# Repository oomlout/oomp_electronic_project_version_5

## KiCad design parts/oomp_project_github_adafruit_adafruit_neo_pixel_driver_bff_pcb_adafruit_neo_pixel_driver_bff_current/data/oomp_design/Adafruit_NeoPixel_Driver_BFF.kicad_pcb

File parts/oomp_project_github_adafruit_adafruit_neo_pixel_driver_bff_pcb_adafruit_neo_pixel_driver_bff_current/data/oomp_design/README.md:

# OOMP KiCad design copy

Open `Adafruit_NeoPixel_Driver_BFF.kicad_pro` (or the `.kicad_pcb` / `.kicad_sch`) in KiCad. Local OOMP libraries are under `libraries/`. Original inputs are preserved in [../original/](../original/).

Only verified unchanged installed KiCad defaults were renamed. Modified, custom, unmatched and unavailable items remain unchanged. Soldering variants are never swapped during conversion. Existing pad coordinates, nets and UUIDs are preserved.

See [conversion_report.yaml](conversion_report.yaml) for every conversion and skip. Copy this directory before editing; regeneration refuses to overwrite edited design files.

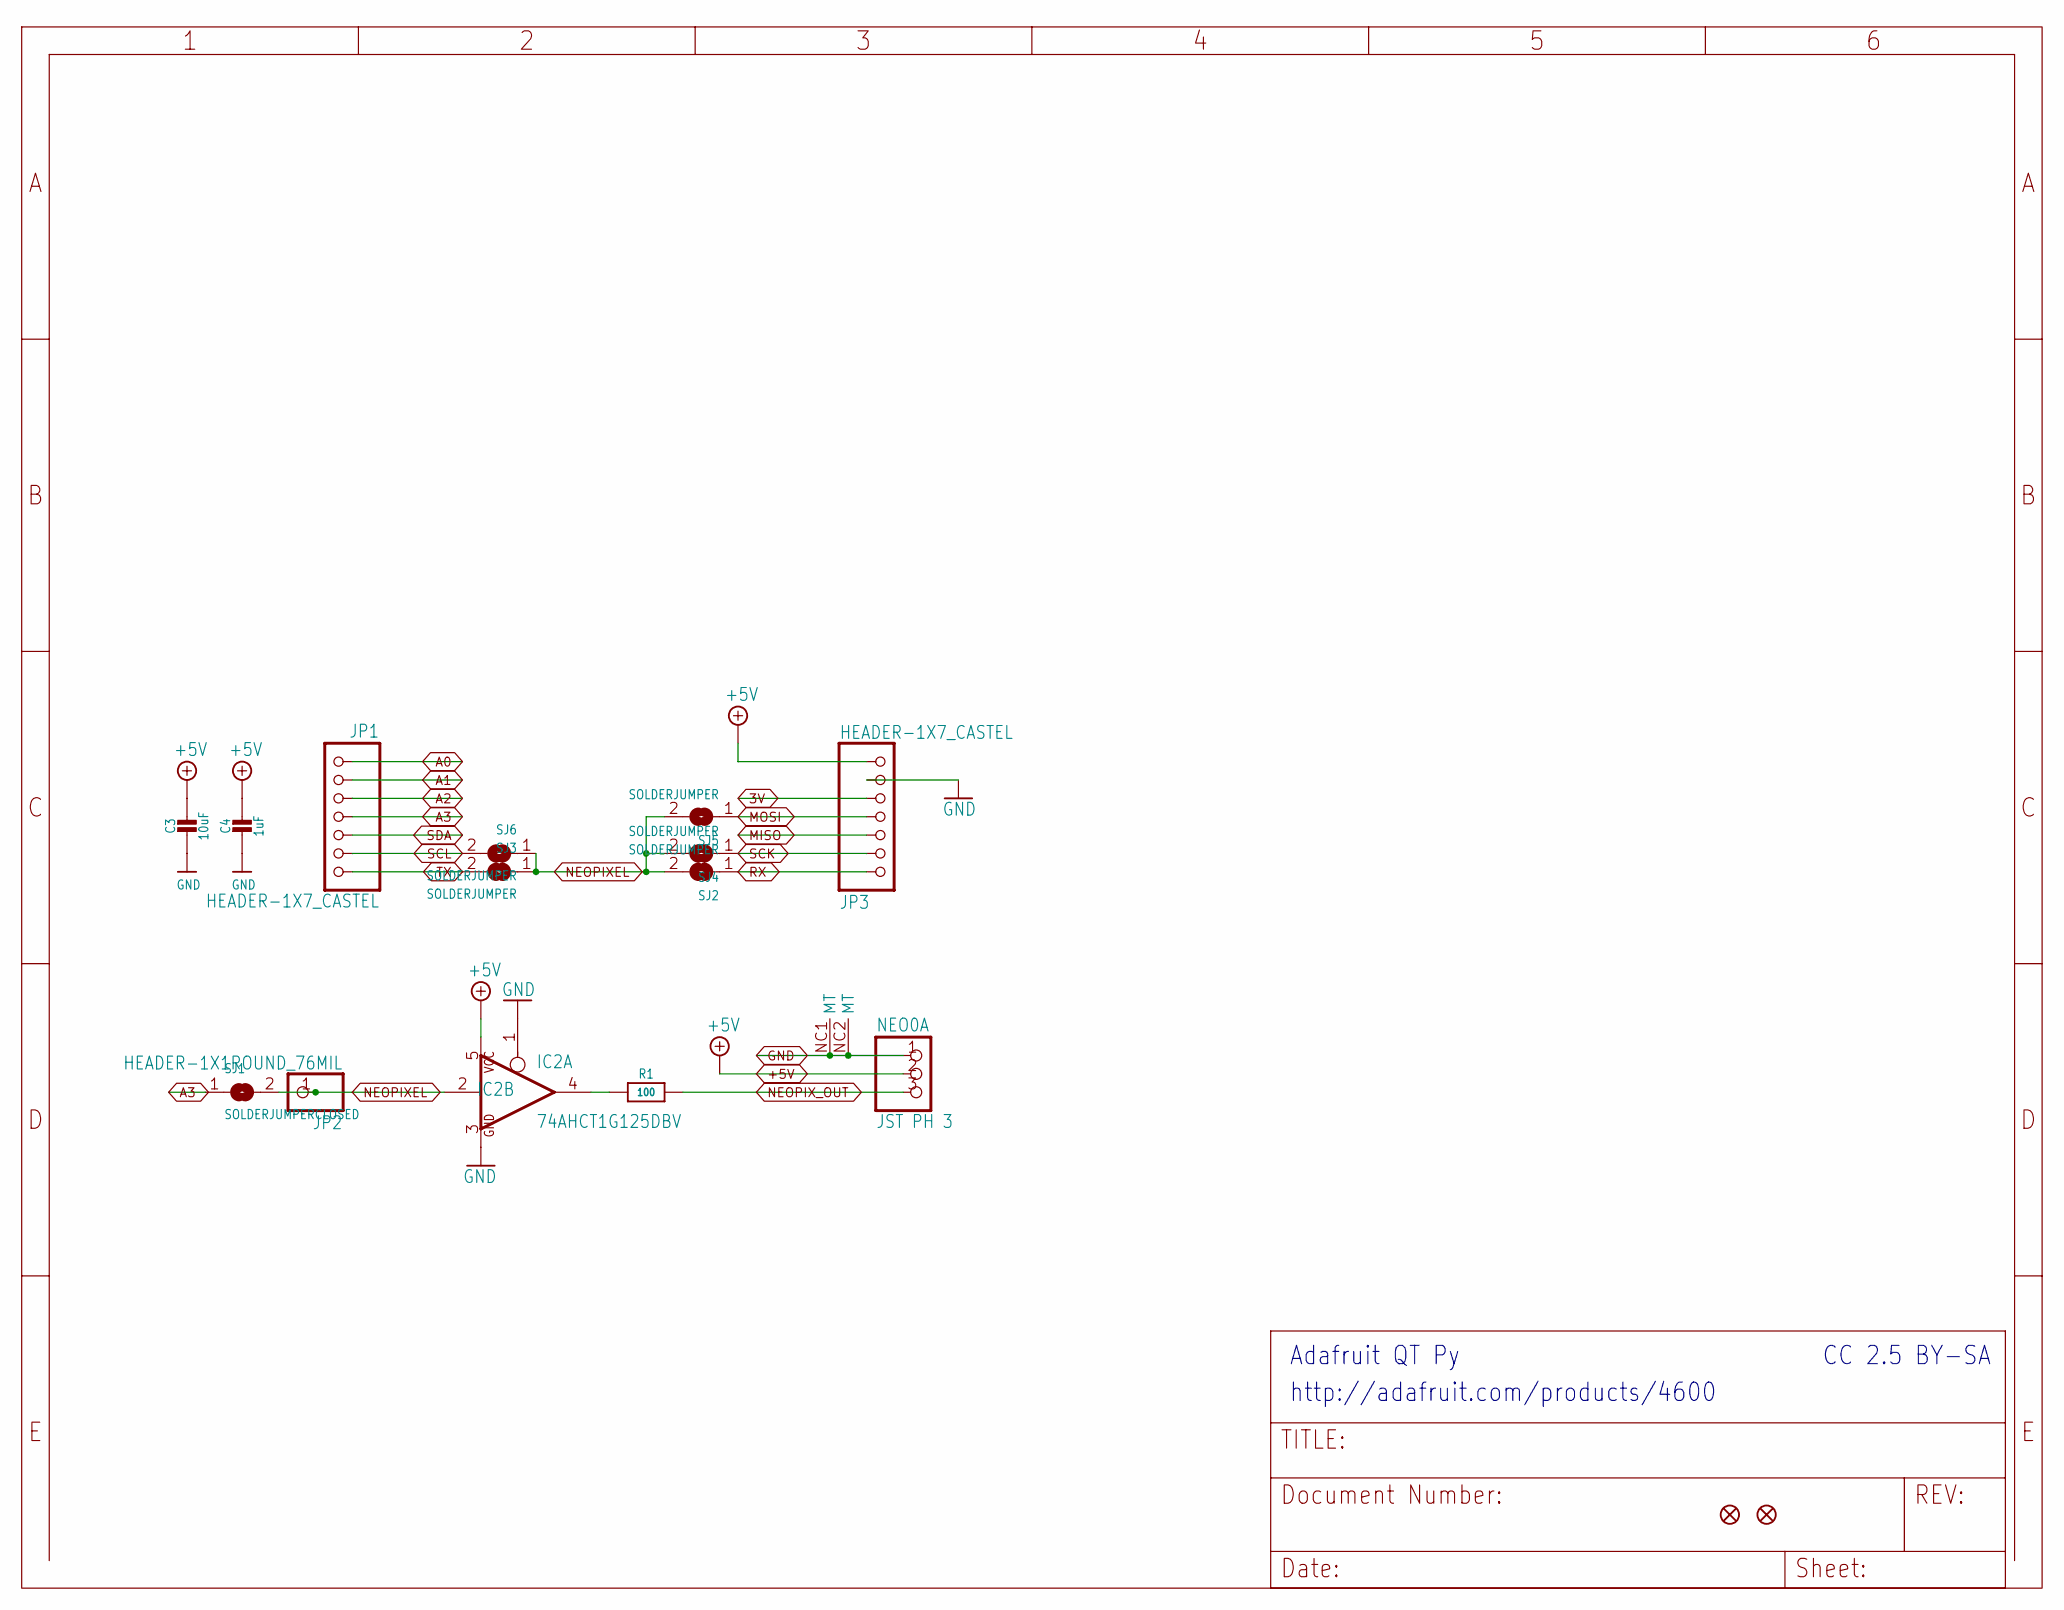
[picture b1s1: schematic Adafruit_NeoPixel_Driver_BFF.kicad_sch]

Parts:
C3: 10uF; 0805-NO
C4: 1uF; 0603-NO
IC2: 74AHCT1G125DBV; SOT23-5
JP1, JP3: HEADER-1X7_CASTEL; 1X07_CASTEL
JP2: HEADER-1X1ROUND_76MIL; 1X01_ROUND_76MIL
NEO0: JST PH 3; JSTPH3
R1: 100; 0603-NO
SJ1: SOLDERJUMPERCLOSED; SOLDERJUMPER_CLOSEDWIRE
SJ2, SJ3, SJ4, SJ5, SJ6: SOLDERJUMPER; SOLDERJUMPER_ARROW_NOPASTE
U$6, U$8: FIDUCIAL_1MM

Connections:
3V: JP3.5, JP3.5C (5)
+5V: C3.1, C4.1, IC2.5 (VCC), JP3.7, JP3.7C (7), NEO0.2
A0: JP1.1, JP1.1C (1)
A1: JP1.2, JP1.2C (2)
A2: JP1.3, JP1.3C (3)
A3: JP1.4, JP1.4C (4), SJ1.1
GND: C3.2, C4.2, IC2.1 (OE), IC2.3 (GND), JP3.6, JP3.6C (6), NEO0.1, NEO0.NC1 (MT), NEO0.NC2 (MT)
MISO: JP3.3, JP3.3C (3)
MOSI: JP3.4, JP3.4C (4), SJ5.1
unnamed: IC2.4 (O), R1.1
NEOPIXEL: IC2.2 (I), JP2.1, SJ1.2, SJ2.2, SJ3.1, SJ4.2, SJ5.2, SJ6.1
NEOPIX_OUT: NEO0.3, R1.2
RX: JP3.1, JP3.1C (1), SJ2.1
SCK: JP3.2, JP3.2C (2), SJ4.1
SCL: JP1.6, JP1.6C (6), SJ6.2
SDA: JP1.5, JP1.5C (5)
TX: JP1.7, JP1.7C (7), SJ3.2

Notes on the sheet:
Adafruit QT Py
http://adafruit.com/products/4600
CC 2.5 BY-SA

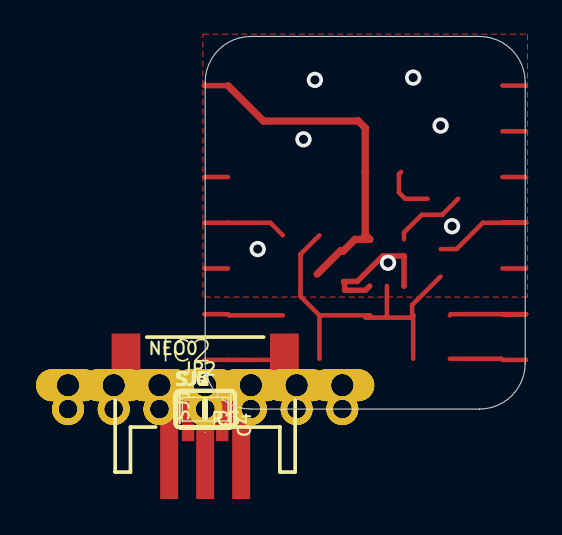
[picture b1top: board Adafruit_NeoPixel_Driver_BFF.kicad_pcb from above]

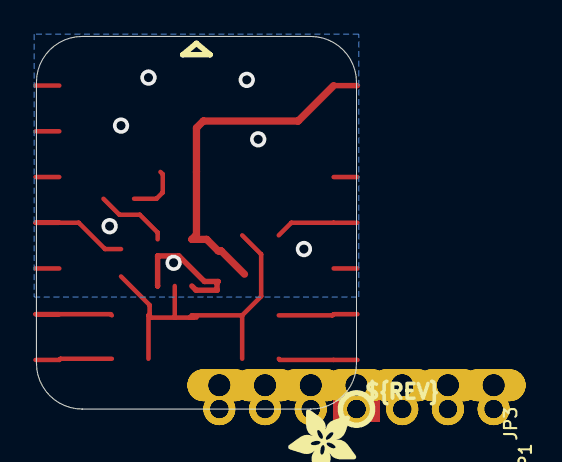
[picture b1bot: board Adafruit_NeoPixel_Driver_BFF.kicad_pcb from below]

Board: 16 copper layers, 17.8 x 20.7 mm, 39 parts (6 on the bottom side), 17 nets.

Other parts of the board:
PLABEL0: PLABEL0
PLABEL1: PLABEL1
PLABEL2: PLABEL2
PLABEL3: PLABEL3
PLABEL4: PLABEL4
PLABEL5: PLABEL5
PLABEL6: PLABEL6
PLABEL7: PLABEL7
PLABEL8: PLABEL8
PLABEL9: PLABEL9
PLABEL10: PLABEL10
PLABEL11: PLABEL11
PLABEL12: PLABEL12
PLABEL13: PLABEL13
PLABEL14: PLABEL14
PLABEL15: PLABEL15
PLABEL16: PLABEL16
PLABEL17: PLABEL17
PLABEL18: PLABEL18
PLABEL19: PLABEL19
PLABEL20: PLABEL20
U$2: ADAFRUIT_3.5MM
U$3: PCBFEAT-REV-040

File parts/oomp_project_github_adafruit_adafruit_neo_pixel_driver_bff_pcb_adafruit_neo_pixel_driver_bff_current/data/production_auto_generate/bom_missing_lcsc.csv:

Designator,Comment,Footprint,OOMP ID,Reason
C3,10uF,Adafruit_NeoPixel_Driver_BFF-import-fps:0805-NO,electronic_capacitor_0805_10_micro_farad,No verified LCSC part number
IC2,74AHCT1G125DBV,Adafruit_NeoPixel_Driver_BFF-import-fps:SOT23-5,,No verified LCSC part number
NEO0,JST PH 3,Adafruit_NeoPixel_Driver_BFF-import-fps:JSTPH3,,No verified LCSC part number
PLABEL0,,Adafruit_NeoPixel_Driver_BFF-import-fps:PLABEL0,,No verified LCSC part number
PLABEL1,,Adafruit_NeoPixel_Driver_BFF-import-fps:PLABEL1,,No verified LCSC part number
PLABEL2,,Adafruit_NeoPixel_Driver_BFF-import-fps:PLABEL2,,No verified LCSC part number
PLABEL3,,Adafruit_NeoPixel_Driver_BFF-import-fps:PLABEL3,,No verified LCSC part number
PLABEL4,,Adafruit_NeoPixel_Driver_BFF-import-fps:PLABEL4,,No verified LCSC part number
PLABEL5,,Adafruit_NeoPixel_Driver_BFF-import-fps:PLABEL5,,No verified LCSC part number
PLABEL6,,Adafruit_NeoPixel_Driver_BFF-import-fps:PLABEL6,,No verified LCSC part number
PLABEL7,,Adafruit_NeoPixel_Driver_BFF-import-fps:PLABEL7,,No verified LCSC part number
PLABEL8,,Adafruit_NeoPixel_Driver_BFF-import-fps:PLABEL8,,No verified LCSC part number
PLABEL9,,Adafruit_NeoPixel_Driver_BFF-import-fps:PLABEL9,,No verified LCSC part number
PLABEL10,,Adafruit_NeoPixel_Driver_BFF-import-fps:PLABEL10,,No verified LCSC part number
PLABEL11,,Adafruit_NeoPixel_Driver_BFF-import-fps:PLABEL11,,No verified LCSC part number
PLABEL12,,Adafruit_NeoPixel_Driver_BFF-import-fps:PLABEL12,,No verified LCSC part number
PLABEL13,,Adafruit_NeoPixel_Driver_BFF-import-fps:PLABEL13,,No verified LCSC part number
PLABEL14,,Adafruit_NeoPixel_Driver_BFF-import-fps:PLABEL14,,No verified LCSC part number
PLABEL15,,Adafruit_NeoPixel_Driver_BFF-import-fps:PLABEL15,,No verified LCSC part number
PLABEL16,,Adafruit_NeoPixel_Driver_BFF-import-fps:PLABEL16,,No verified LCSC part number
PLABEL17,,Adafruit_NeoPixel_Driver_BFF-import-fps:PLABEL17,,No verified LCSC part number
PLABEL18,,Adafruit_NeoPixel_Driver_BFF-import-fps:PLABEL18,,No verified LCSC part number
PLABEL19,,Adafruit_NeoPixel_Driver_BFF-import-fps:PLABEL19,,No verified LCSC part number
PLABEL20,,Adafruit_NeoPixel_Driver_BFF-import-fps:PLABEL20,,No verified LCSC part number
U$2,,Adafruit_NeoPixel_Driver_BFF-import-fps:ADAFRUIT_3.5MM,,No verified LCSC part number
U$3,,Adafruit_NeoPixel_Driver_BFF-import-fps:PCBFEAT-REV-040,,No verified LCSC part number
U$6,FIDUCIAL_1MM,Adafruit_NeoPixel_Driver_BFF-import-fps:FIDUCIAL_1MM,,No verified LCSC part number
U$8,FIDUCIAL_1MM,Adafruit_NeoPixel_Driver_BFF-import-fps:FIDUCIAL_1MM,,No verified LCSC part number

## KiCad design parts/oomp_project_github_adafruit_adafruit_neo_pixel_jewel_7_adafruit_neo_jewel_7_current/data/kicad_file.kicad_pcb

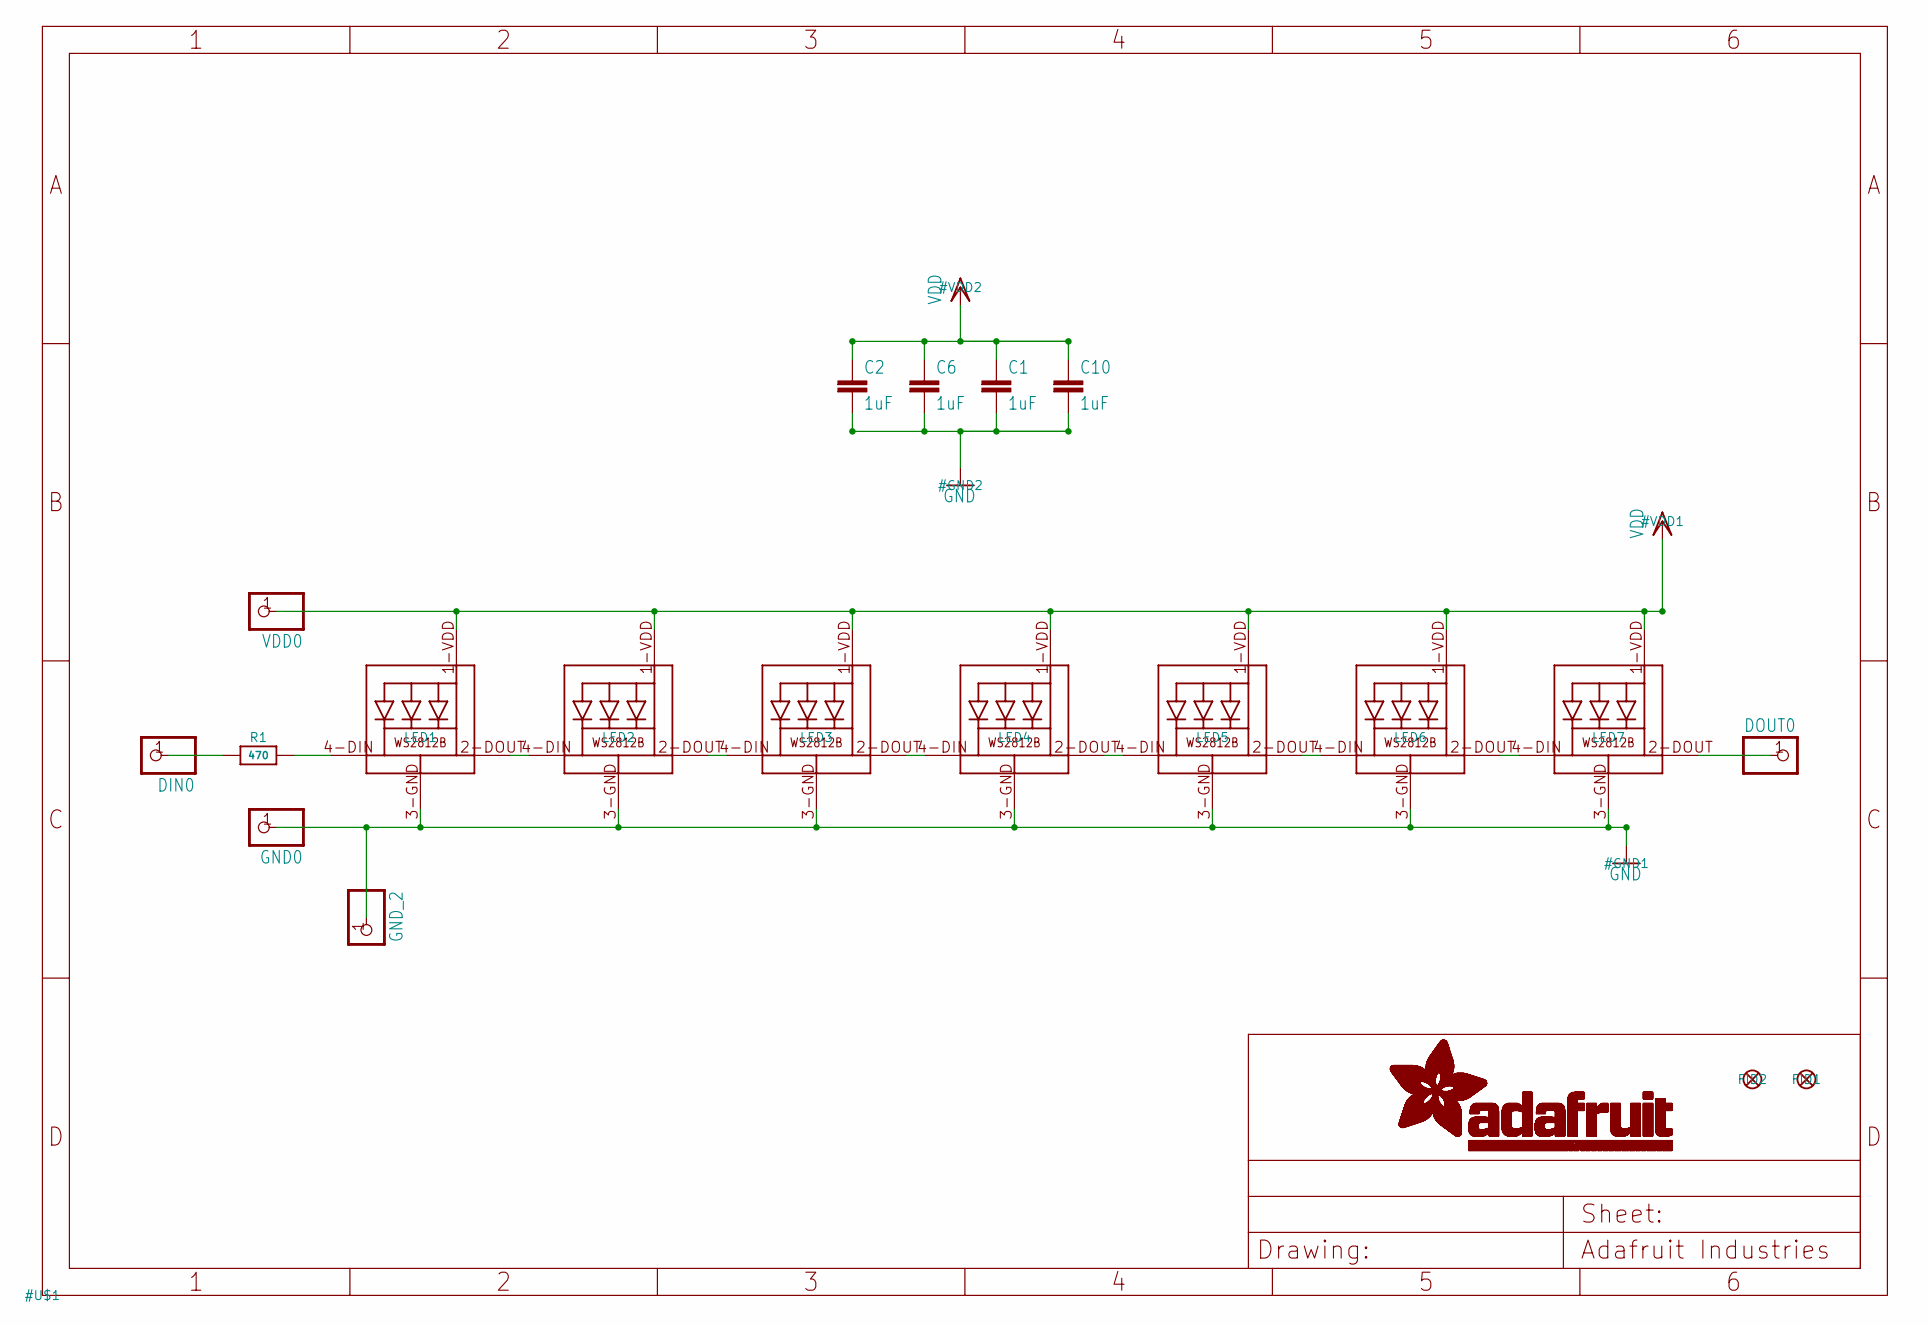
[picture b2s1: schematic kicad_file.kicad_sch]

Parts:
C1, C2, C6, C10: 1uF; C0603
DIN0: PINHD-1X1CB; 1X01-CLEANBIG
DOUT0: PINHD-1X1CB; 1X01-CLEANBIG
FID1, FID2: FIDUCIAL""; FIDUCIAL_1MM
GND0: PINHD-1X1CB; 1X01-CLEANBIG
GND_2: PINHD-1X1CB; 1X01-CLEANBIG
LED1, LED2, LED3, LED4, LED5, LED6, LED7: WS2812B5050; WS2812B
R1: 470; 0603-NO
VDD0: PINHD-1X1CB; 1X01-CLEANBIG

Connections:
GND: C1.2, C2.2, C6.2, C10.2, GND0.1, GND_2.1, LED1.3-GND (GND), LED2.3-GND (GND), LED3.3-GND (GND), LED4.3-GND (GND), LED5.3-GND (GND), LED6.3-GND (GND), LED7.3-GND (GND)
unnamed: LED1.2-DOUT (DO), LED2.4-DIN (DI)
unnamed: LED2.2-DOUT (DO), LED3.4-DIN (DI)
unnamed: LED3.2-DOUT (DO), LED4.4-DIN (DI)
unnamed: LED4.2-DOUT (DO), LED5.4-DIN (DI)
unnamed: LED5.2-DOUT (DO), LED6.4-DIN (DI)
unnamed: LED6.2-DOUT (DO), LED7.4-DIN (DI)
unnamed: DOUT0.1, LED7.2-DOUT (DO)
unnamed: LED1.4-DIN (DI), R1.2
unnamed: DIN0.1, R1.1
VDD: C1.1, C2.1, C6.1, C10.1, LED1.1-VDD (VDD), LED2.1-VDD (VDD), LED3.1-VDD (VDD), LED4.1-VDD (VDD), LED5.1-VDD (VDD), LED6.1-VDD (VDD), LED7.1-VDD (VDD), VDD0.1

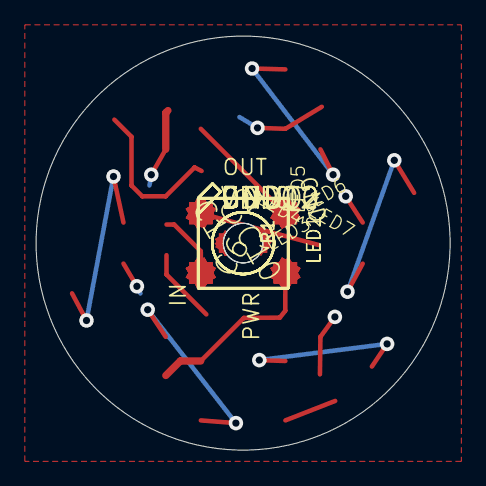
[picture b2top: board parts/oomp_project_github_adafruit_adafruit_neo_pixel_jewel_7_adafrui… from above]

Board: 2 copper layers, 23.0 x 23.0 mm, 22 parts (1 on the bottom side), 11 nets.

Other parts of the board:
U$3: ADAFRUIT_5MM
UNK_HOLE_0: dummyfp0
UNK_HOLE_1: dummyfp1

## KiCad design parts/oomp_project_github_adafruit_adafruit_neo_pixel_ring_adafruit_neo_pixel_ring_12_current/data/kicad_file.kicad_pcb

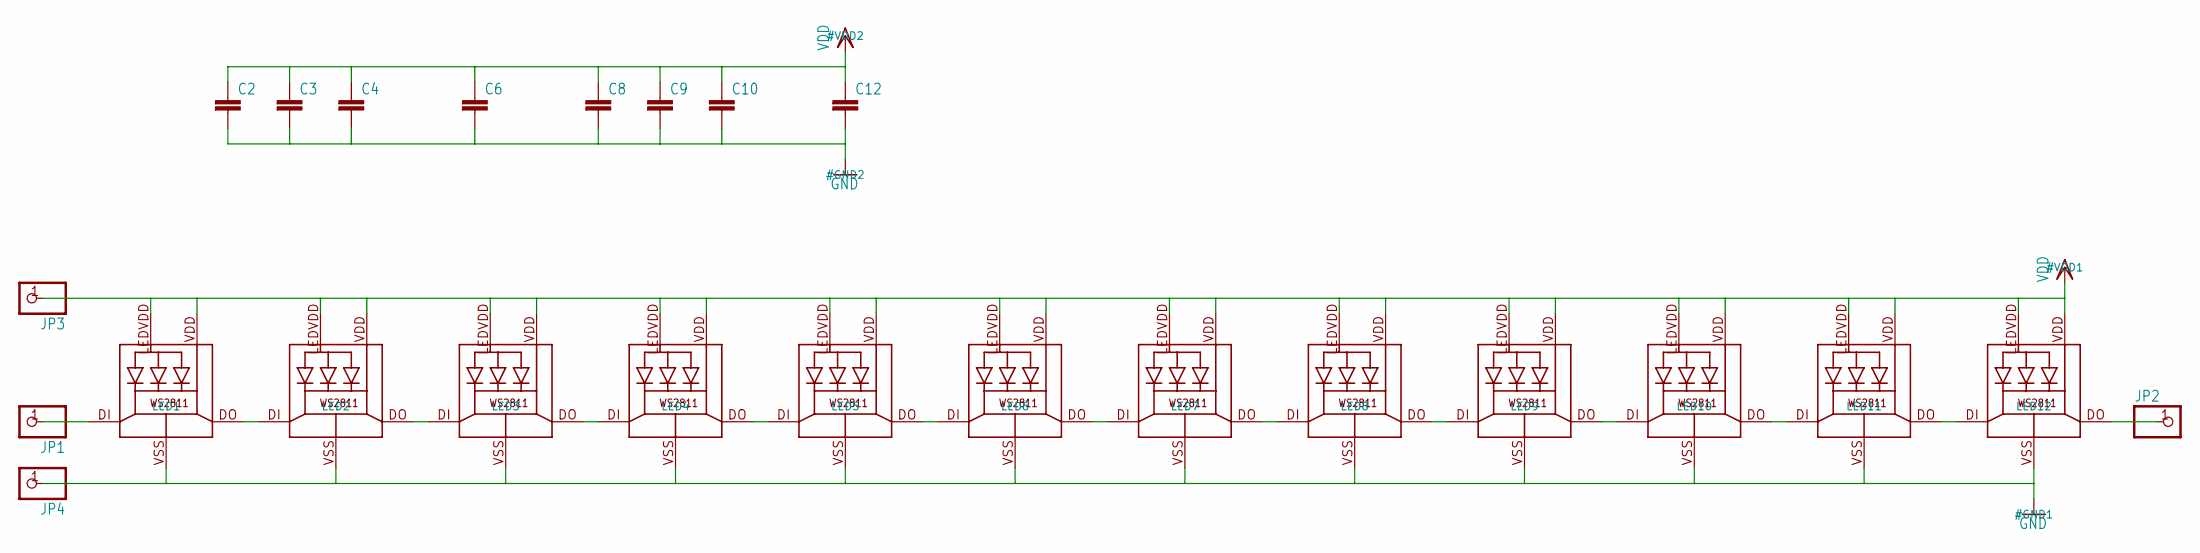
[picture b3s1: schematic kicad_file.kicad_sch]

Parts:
C2, C3, C4, C6, C8, C9, C10, C12: C-EUC0603; C0603
JP1, JP2, JP3, JP4: PINHD-1X1CB; 1X01-CLEANBIG
LED1, LED2, LED3, LED4, LED5, LED6, LED7, LED8, LED9, LED10, LED11, LED12: WS28115050

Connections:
GND: C2.2, C3.2, C4.2, C6.2, C8.2, C9.2, C10.2, C12.2, JP4.1, LED1.VSS (GND), LED2.VSS (GND), LED3.VSS (GND), LED4.VSS (GND), LED5.VSS (GND), LED6.VSS (GND), LED7.VSS (GND), LED8.VSS (GND), LED9.VSS (GND), LED10.VSS (GND), LED11.VSS (GND), LED12.VSS (GND)
unnamed: LED1.DO, LED2.DI
unnamed: LED2.DO, LED3.DI
unnamed: LED3.DO, LED4.DI
unnamed: LED4.DO, LED5.DI
unnamed: LED5.DO, LED6.DI
unnamed: LED6.DO, LED7.DI
unnamed: LED7.DO, LED8.DI
unnamed: LED8.DO, LED9.DI
unnamed: LED9.DO, LED10.DI
unnamed: LED10.DO, LED11.DI
unnamed: LED11.DO, LED12.DI
unnamed: JP1.1, LED1.DI
unnamed: JP2.1, LED12.DO
VDD: C2.1, C3.1, C4.1, C6.1, C8.1, C9.1, C10.1, C12.1, JP3.1, LED1.LEDVDD, LED1.VDD, LED2.LEDVDD, LED2.VDD, LED3.LEDVDD, LED3.VDD, LED4.LEDVDD, LED4.VDD, LED5.LEDVDD, LED5.VDD, LED6.LEDVDD, LED6.VDD, LED7.LEDVDD, LED7.VDD, LED8.LEDVDD, LED8.VDD, LED9.LEDVDD, LED9.VDD, LED10.LEDVDD, LED10.VDD, LED11.LEDVDD, LED11.VDD, LED12.LEDVDD, LED12.VDD

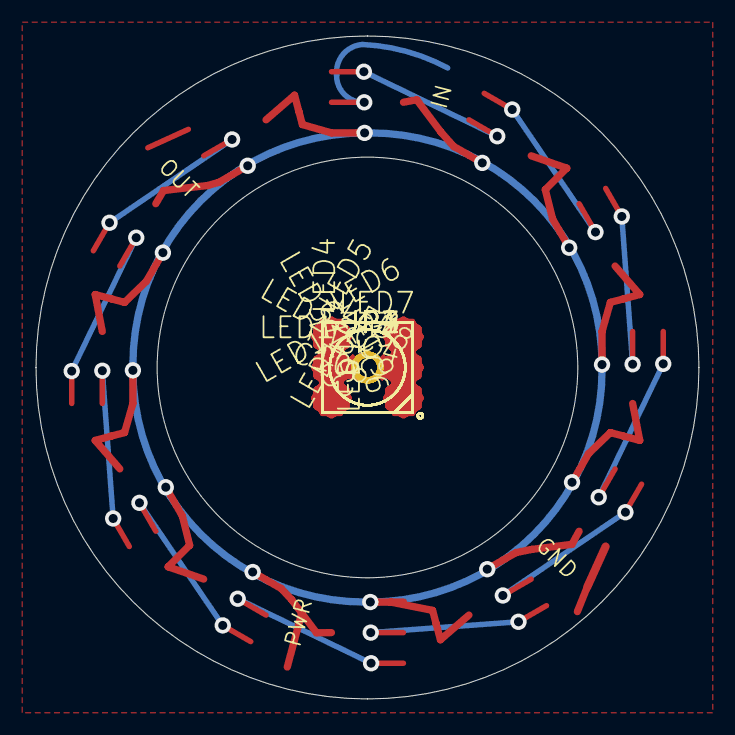
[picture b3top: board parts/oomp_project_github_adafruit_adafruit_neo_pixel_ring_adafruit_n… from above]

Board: 2 copper layers, 36.8 x 36.8 mm, 27 parts (1 on the bottom side), 15 nets.

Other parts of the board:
U$1, U$2: GUIDE-STAR-12
U$3: ADAFRUIT_5MM

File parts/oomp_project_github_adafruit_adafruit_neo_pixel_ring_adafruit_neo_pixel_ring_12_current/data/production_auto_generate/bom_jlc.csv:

Comment,Designator,Footprint,LCSC Part #
,"JP1,JP2,JP3,JP4",Adafruit NeoPixel Ring 12-import-fps:1X01-CLEANBIG,C7501259
,U$3,Adafruit NeoPixel Ring 12-import-fps:ADAFRUIT_5MM,
,"C2,C3,C4,C6,C8,C9,C10,C12",Adafruit NeoPixel Ring 12-import-fps:C0603,
,"U$1,U$2",Adafruit NeoPixel Ring 12-import-fps:GUIDE-STAR-12,
WS28115050,"LED1,LED2,LED3,LED4,LED5,LED6,LED7,LED8,LED9,LED10,LED11,LED12",Adafruit NeoPixel Ring 12-import-fps:WS28115050,
